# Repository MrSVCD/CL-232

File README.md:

# CL-232

## In progress - Ver 0.4

This is a current loop to 5V Logic/RS232 adapter for using old old hardware or serial communication over a long distance, old old school style.

The adapter is based on B&B electronics [design](Documents/B&B%20Electronics%20-%20232CL9R.pdf) with some additions sutch as running of a Amiga serial ports power or skipping the whole RS232 to 5V Logic converter part and run it of a USB to TTL232 adapter. 

I also changed the 5V Logic <-> RS232 chip to a single MAX3232 which has the added benefit to only need +5v instead of the old design needing +/-12v, this also makes the adapter able to run on USB power. The Current Loop probably needs more than 5v to get any length going but it should be possible to get a short link going with just 5v, all the old documentation I have found uses 12v or more. 

## Current Limiter
In the folder [CurrentLimiter](CurrentLimiter) there is a simple Current Limiter based on a LM317 and a 62Ω resistor. This current limiter works on a loop up to 40 volts.

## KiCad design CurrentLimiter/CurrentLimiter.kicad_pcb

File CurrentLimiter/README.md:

# Current Limiter

This is a simple PCB that uses a LM317 and a 68Ω resistor to make a 20mA current limiter that adjusts for different voltages (up to 40volts).

The circuit is so simple that a PCB is not really necessary. If you build one without a PCB, remember that the exposed metal on the TO-220 version is connected to voltage out and should be isolated if it needs cooling.

## Resistor value examples:
| Target mA | Exact Ω | Nearest E24 resistor| Resulting mA |
|----------:|--------:|------------:|----------:|
|         5 |  256,00 |         270 |      4,74 |
|        10 |  128,00 |         120 |     10,67 |
|        20 |   64,00 |          62 |     20,65 |
|        30 |   42,67 |          43 |     29,77 |
|        40 |   32,00 |          33 |     38,79 |
|        50 |   25,60 |          27 |     47,41 |

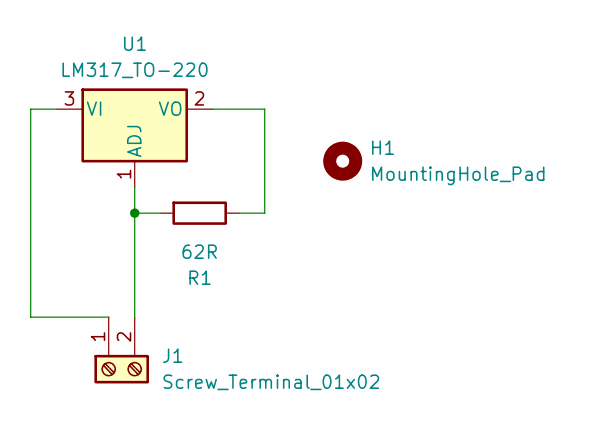
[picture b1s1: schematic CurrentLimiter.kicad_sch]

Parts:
H1: MountingHole_Pad; MountingHole_3.2mm_M3
J1: Screw_Terminal_01x02; TerminalBlock_Phoenix_MKDS-1,5-2-5.08_1x02_P5.08mm_Horizont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
R1: 62R; R_Axial_DIN0207_L6.3mm_D2.5mm_P2.54mm_Vertical
U1: LM317_TO-220; TO-220-3_Horizontal_TabDown

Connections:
unnamed: J1.1, U1.3 (VI)
unnamed: J1.2, R1.2, U1.1 (ADJ)
unnamed: R1.1, U1.2 (VO)

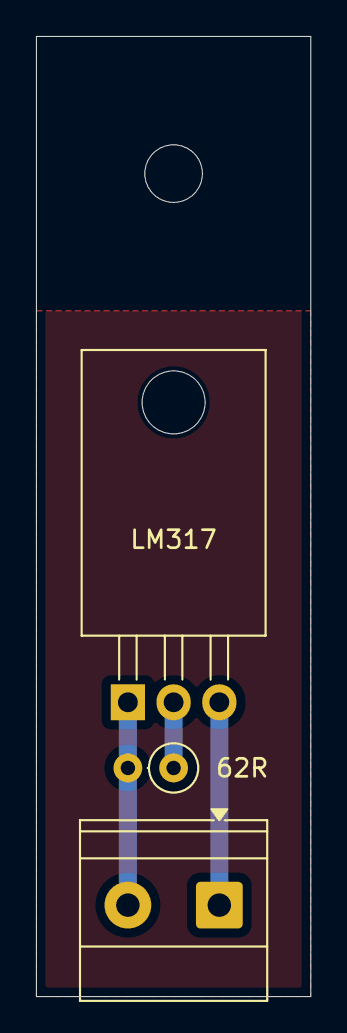
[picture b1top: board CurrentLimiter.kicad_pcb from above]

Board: 2 copper layers, 15.2 x 53.3 mm, 4 parts (0 on the bottom side), 3 nets.

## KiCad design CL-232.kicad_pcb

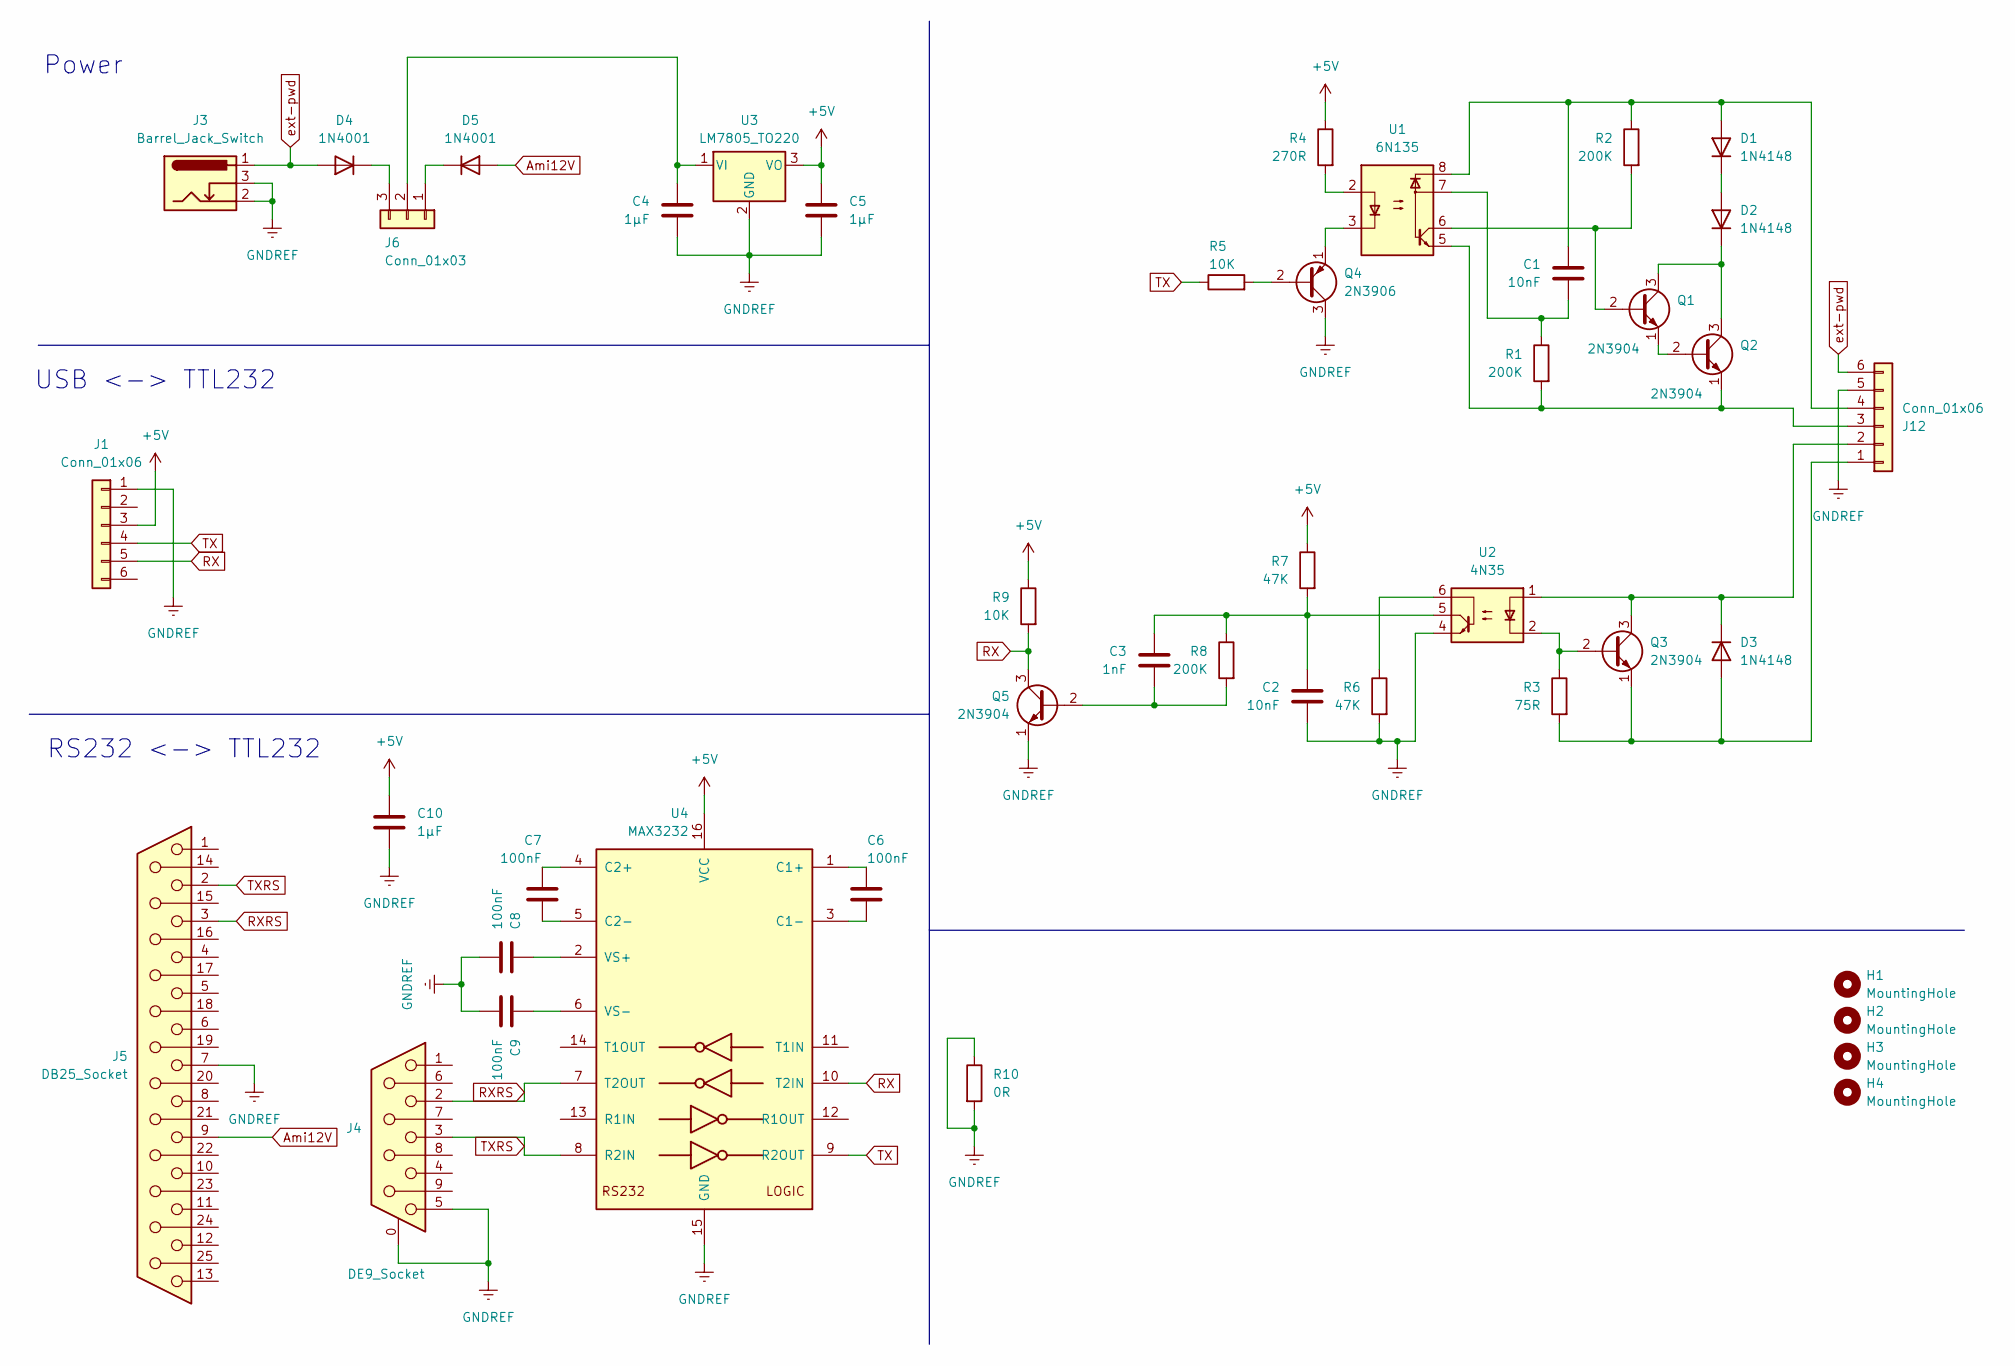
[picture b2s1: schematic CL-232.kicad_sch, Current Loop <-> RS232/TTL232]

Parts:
C1, C2: 10nF; C_Disc_D5.0mm_W2.5mm_P2.50mm
C3: 1nF; C_Disc_D5.0mm_W2.5mm_P2.50mm
C4, C5, C10: 1µF; C_Disc_D5.0mm_W2.5mm_P5.00mm
C6, C7, C8, C9: 100nF; C_Disc_D5.0mm_W2.5mm_P2.50mm
D1, D2, D3: 1N4148; D_DO-35_SOD27_P7.62mm_Horizontal
D4, D5: 1N4001; D_DO-41_SOD81_P10.16mm_Horizontal
H1, H2, H3, H4: MountingHole; MountingHole_3.2mm_M3_ISO14580
J1: Conn_01x06; PinHeader_1x06_P2.54mm_Vertical
J3: Barrel_Jack_Switch; BarrelJack_Horizontal
J4: DE9_Socket; DSUB-9_Socket_Horizontal_P2.77x2.84mm_EdgePinOffset4.94mm_H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
J5: DB25_Socket; DSUB-25_Socket_EdgeMount_P2.77mm
J6: Conn_01x03; PinHeader_1x03_P2.54mm_Horizontal
J12: Conn_01x06; PhoenixContact_MC_1,5_6-G-5.08_1x06_P5.08mm_Horizontal
Q1, Q2: 2N3904; TO-92L_HandSolder
Q3, Q5: 2N3904; TO-92_HandSolder
Q4: 2N3906; TO-92L_HandSolder
R1, R2, R8: 200K; R_Axial_DIN0207_L6.3mm_D2.5mm_P10.16mm_Horizontal
R3: 75R; R_Axial_DIN0207_L6.3mm_D2.5mm_P10.16mm_Horizontal
R4: 270R; R_Axial_DIN0207_L6.3mm_D2.5mm_P10.16mm_Horizontal
R5, R9: 10K; R_Axial_DIN0207_L6.3mm_D2.5mm_P10.16mm_Horizontal
R6, R7: 47K; R_Axial_DIN0207_L6.3mm_D2.5mm_P10.16mm_Horizontal
R10: 0R; R_Axial_DIN0204_L3.6mm_D1.6mm_P5.08mm_Horizontal
U1: 6N135; DIP-8_W7.62mm
U2: 4N35; DIP-6_W7.62mm
U3: LM7805_TO220; TO-220F-3_Horizontal_TabDown
U4: MAX3232; DIP-16_W7.62mm_Socket_LongPads

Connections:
+5V: C5.1, C10.1, J1.3, R4.1, R7.1, R9.1, U3.3 (VO), U4.16 (VCC)
Ami12V: D5.2 (A), J5.9
GNDREF: C2.2, C4.2, C5.2, C8.2, C9.2, C10.2, J1.1, J3.2, J3.3, J4.0 (PAD), J4.5, J5.7, J12.5, Q4.3 (C), Q5.1 (E), R6.2, R10.1, R10.2, U2.4, U3.2 (GND), U4.15 (GND)
unnamed: C1.2, R1.1, U1.7
unnamed: C2.1, C3.1, R7.2, R8.1, U2.5
unnamed: C1.1, D1.2 (A), J12.4, R2.1, U1.8
unnamed: D1.1 (K), D2.2 (A)
unnamed: D2.1 (K), Q1.3 (C), Q2.3 (C)
unnamed: D3.2 (A), J12.1, Q3.1 (E), R3.2
unnamed: D3.1 (K), J12.2, Q3.3 (C), U2.1
unnamed: D4.1 (K), J6.3
unnamed: D5.1 (K), J6.1
unnamed: C4.1, J6.2, U3.1 (VI)
unnamed: J12.3, Q2.1 (E), R1.2, U1.5
unnamed: Q1.2 (B), R2.2, U1.6
unnamed: Q1.1 (E), Q2.2 (B)
unnamed: Q3.2 (B), R3.1, U2.2
unnamed: Q4.2 (B), R5.2
unnamed: Q4.1 (E), U1.3
unnamed: C3.2, Q5.2 (B), R8.2
unnamed: R4.2, U1.2
unnamed: R6.1, U2.6
unnamed: C6.1, U4.1 (C1+)
unnamed: C6.2, U4.3 (C1-)
unnamed: C7.1, U4.4 (C2+)
unnamed: C7.2, U4.5 (C2-)
unnamed: C8.1, U4.2 (VS+)
unnamed: C9.1, U4.6 (VS-)
RX: J1.5, Q5.3 (C), R9.2, U4.10 (T2IN)
RXRS: J4.2, J5.3, U4.7 (T2OUT)
TX: J1.4, R5.1, U4.9 (R2OUT)
TXRS: J4.3, J5.2, U4.8 (R2IN)
ext-pwd: D4.2 (A), J3.1, J12.6

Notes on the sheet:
Power
RS232 <-> TTL232
USB <-> TTL232

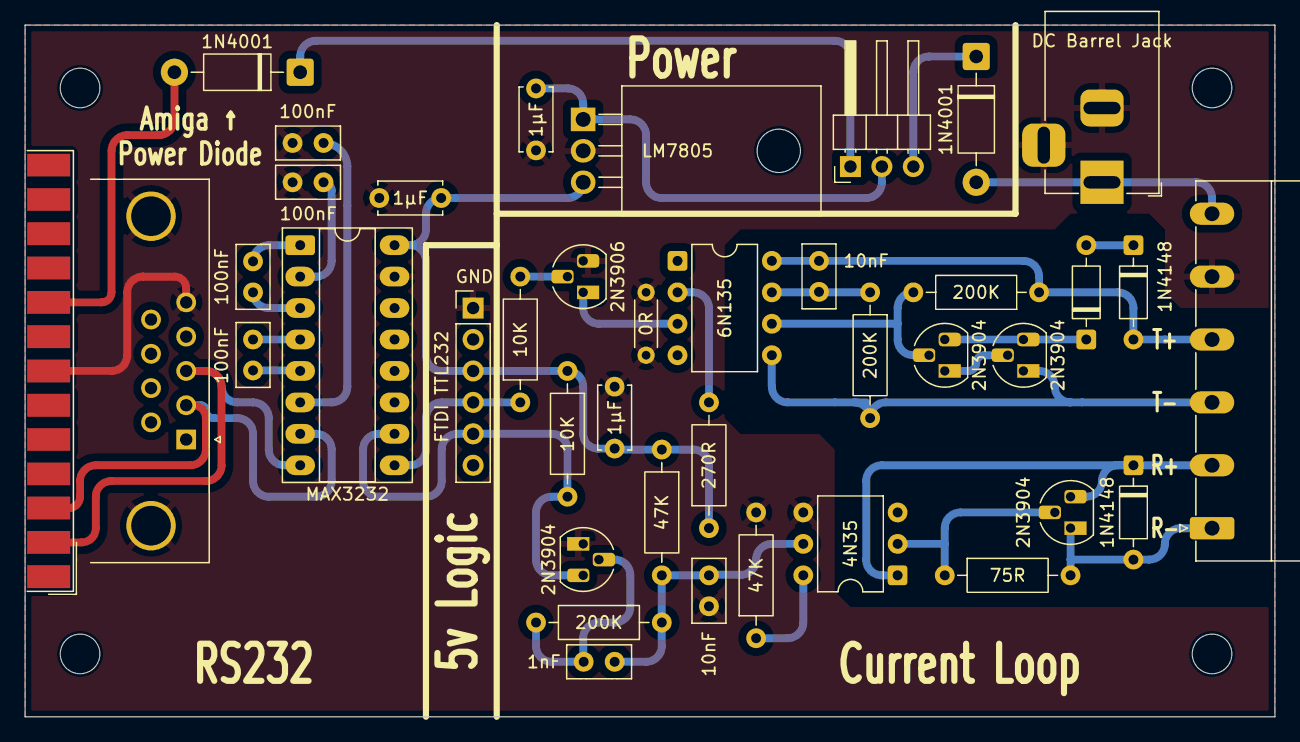
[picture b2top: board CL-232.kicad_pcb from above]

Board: 2 copper layers, 101.0 x 55.9 mm, 44 parts (0 on the bottom side), 33 nets.

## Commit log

2025-12-30 Upload files to "/"
2025-12-30 Upload files to "Documents"
2025-12-30 2025-12-30 21:43
2025-12-30 PDF added
2025-12-31 2025-12-31
2025-12-31 First Draft
2025-12-31 First revision is done.
2025-12-31 More slime line
2026-01-01 Version 0.2
2026-01-01 Version 0.2.1
2026-01-03 CurrentLimiter added
2026-01-03 Added some documentation
2026-01-04 Added a ReadMe
2026-01-04 Version 0.3
2026-01-04 Update README.md
    Version 0.3
2026-01-05 Version 0.4
